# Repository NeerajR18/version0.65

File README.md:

# version0.65

version0.65 is an almost 65% keyboard. It is a bluetooth keyboard, using the SuperMini nRF52840 board, which is pin compatible with the nice!nano v2.
It has a built in battery along with a On/Off switch.

The keyboard is hotswap, with gateron hotswap sockets and Gateron Blue switches.

The PCB was designed in KiCad and the case was designed in Autodesk Fusion. The footprints for the switches have been taken from the marbastlib library - https://github.com/ebastler/marbastlib

This Keyboard was made for Hack Club KEEB.

Note: This is still a WIP. Please copy at your own risk.

## Repository Guide
```
version1/
|── PCB/
|   |── version0.65.kicad_pro
|   |── version0.65.kicad_pcb
|   |── version0.65.kicad_sch
|   └── fp-lib-table
|
|── CAD/
|   |── Base/
|   |   |── version0.65-base-left.step
|   |   |── version0.65-base-middle.step
|   |   └── version0.65-base-right.step
|   |   
|   |──── Top/
|   |     |── version0.65-plate-left.step
|   |     └── version0.65-plate-right.step
|   |
|   |── version0.65-assembly.step
|   └── version0.65.f3z
| 
|── Production/   
|    |── gerbers.zip/
|    |
|    |── STL Files/
|    |   |─── version0.65-base/
|    |   |    |── version0.65-base-left.stl
|    |   |    |── version0.65-base-middle.stl
|    |   |    └── version0.65-base-right.stl
|    |   |
|    |   └─── version0.65-plate/
|    |        |── version0.65-plate-left.stl
|    |        └── version0.65-plate-right.stl
|    |
|    └── STEP Files/
|           |─── version0.65-base/
|           |      |── version0.65-base-left.step
|           |      |── version0.65-base-middle.step
|           |      └── version0.65-base-right.step
|           |
|           └──── version0.65-plate/
|                   |── version0.65-plate-left.step
|                   └── version0.65-plate-right.step
|
|── Assets/
|    |── Keycaps/
|    |── MX Switch/
|    └── nice!nano/
|
|── Firmware/
|
|── BOM.csv
|── journal.md
└── README.md
```

## Schematic
##### Overall Schematic

## PCB
##### PCB Front without GND Plane

##### PCB Front with GND Plane

##### PCB Back without GND Plane

##### PCB Back with GND Plane

## CAD
The case has been split to accomodate 3D printing. The plates and base have small pegs and holes for assembly.

#### Full Assembly
##### Top View

#####  Side View

#### Top Plate
##### Top View

#####  Side View

#### Base
##### Top View

#####  Side View

## Firmware
version0.65 uses ZMK firmare. While the firmware has not been tested IRL, it can be found in a separate repository.

Firmware repository- https://github.com/NeerajR18/zmk-config-version0.65

## Bill of Materials
| Part Name | Quantity | Unit Price (USD) | Ext. Price (USD) | Link |
|-----------|---------:|-----------------:|-----------------:|------|
| nRF52840 Development Board (Compatible with nice!nano) | 1 | 8.00 | 8.00 | https://robu.in/product/promicro-nrf52840-development-board/ |
| Gradient Keycaps | 1 | 13.66 | 13.66 | https://stackskb.com/store/veekos-gradient-keycaps-cherry-profile-135-keys/ |
| Gateron Hotswap Sockets | 66 | 0.11 | 7.00 | https://stackskb.com/store/gateron-hotswap-sockets/ |
| Gateron G Pro 3.0 Switch (Pack of 10) | 7 | 2.10 | 14.71 | https://meckeys.com/shop/accessories/keyboard-accessories/key-switches/gateron-g-pro-3-0-switch/ |
| OS102011MA1QN1 | 1 | 0.38 | 0.38 | https://robu.in/product/os102011ma1qn1-ck-100ma-single-pole-double-throw-spdt-12v-10000-times-plugin-slide-switches-rohs/ |
| S2B-PH-SM4-TB | 1 | 0.42 | 0.42 | https://robu.in/product/s2b-ph-sm4-tblfsn-jst-1x2p-2p-ph-tin-2-25%E2%84%8385%E2%84%83-2a-1-2mm-copper-alloy-horizontal-attachment-smdp2mmsurface-mount%EF%BC%8Cright-angle-wire-to-board-connector-rohs/ |
| 1N4148W-T4 | 66 | 0.015 | 0.99 | https://sharvielectronics.com/product/1n4148w-t4-high-speed-fast-switching-diode-sod-123-package/ |
| YY503040-JST-PH | 1 | 2.31 | 2.31 | https://sharvielectronics.com/product/3-7v-1100mah-lipo-rechargeable-battery-with-jst-ph-2mm-connector/ |
| PCB from Robu | 5 | 8.83 | 44.28 | https://robu.in/ |
| Cherry Stabilizer Set (GEON AND C3) | 1 | 7.36 | 7.36 | https://neomacro.in/products/cherry-stabilizer-set-geon-and-c3?_pos=3&_sid=9a6134911&_ss=r |
| M3 Heatset Insert | 20 | 0.025 | 0.50 | https://onlyscrews.in/products/m3-x-3mm-brass-threaded-inserts |
| M3 × 16mm Screws | 20 | 0.023 | 0.46 | https://onlyscrews.in/products/hex-allen-csk-m3-x-16-screw-pack-of-20 |
| Shipping charges |-| - | 7 | - |
| **Total** |  |  | **107.07** |  |

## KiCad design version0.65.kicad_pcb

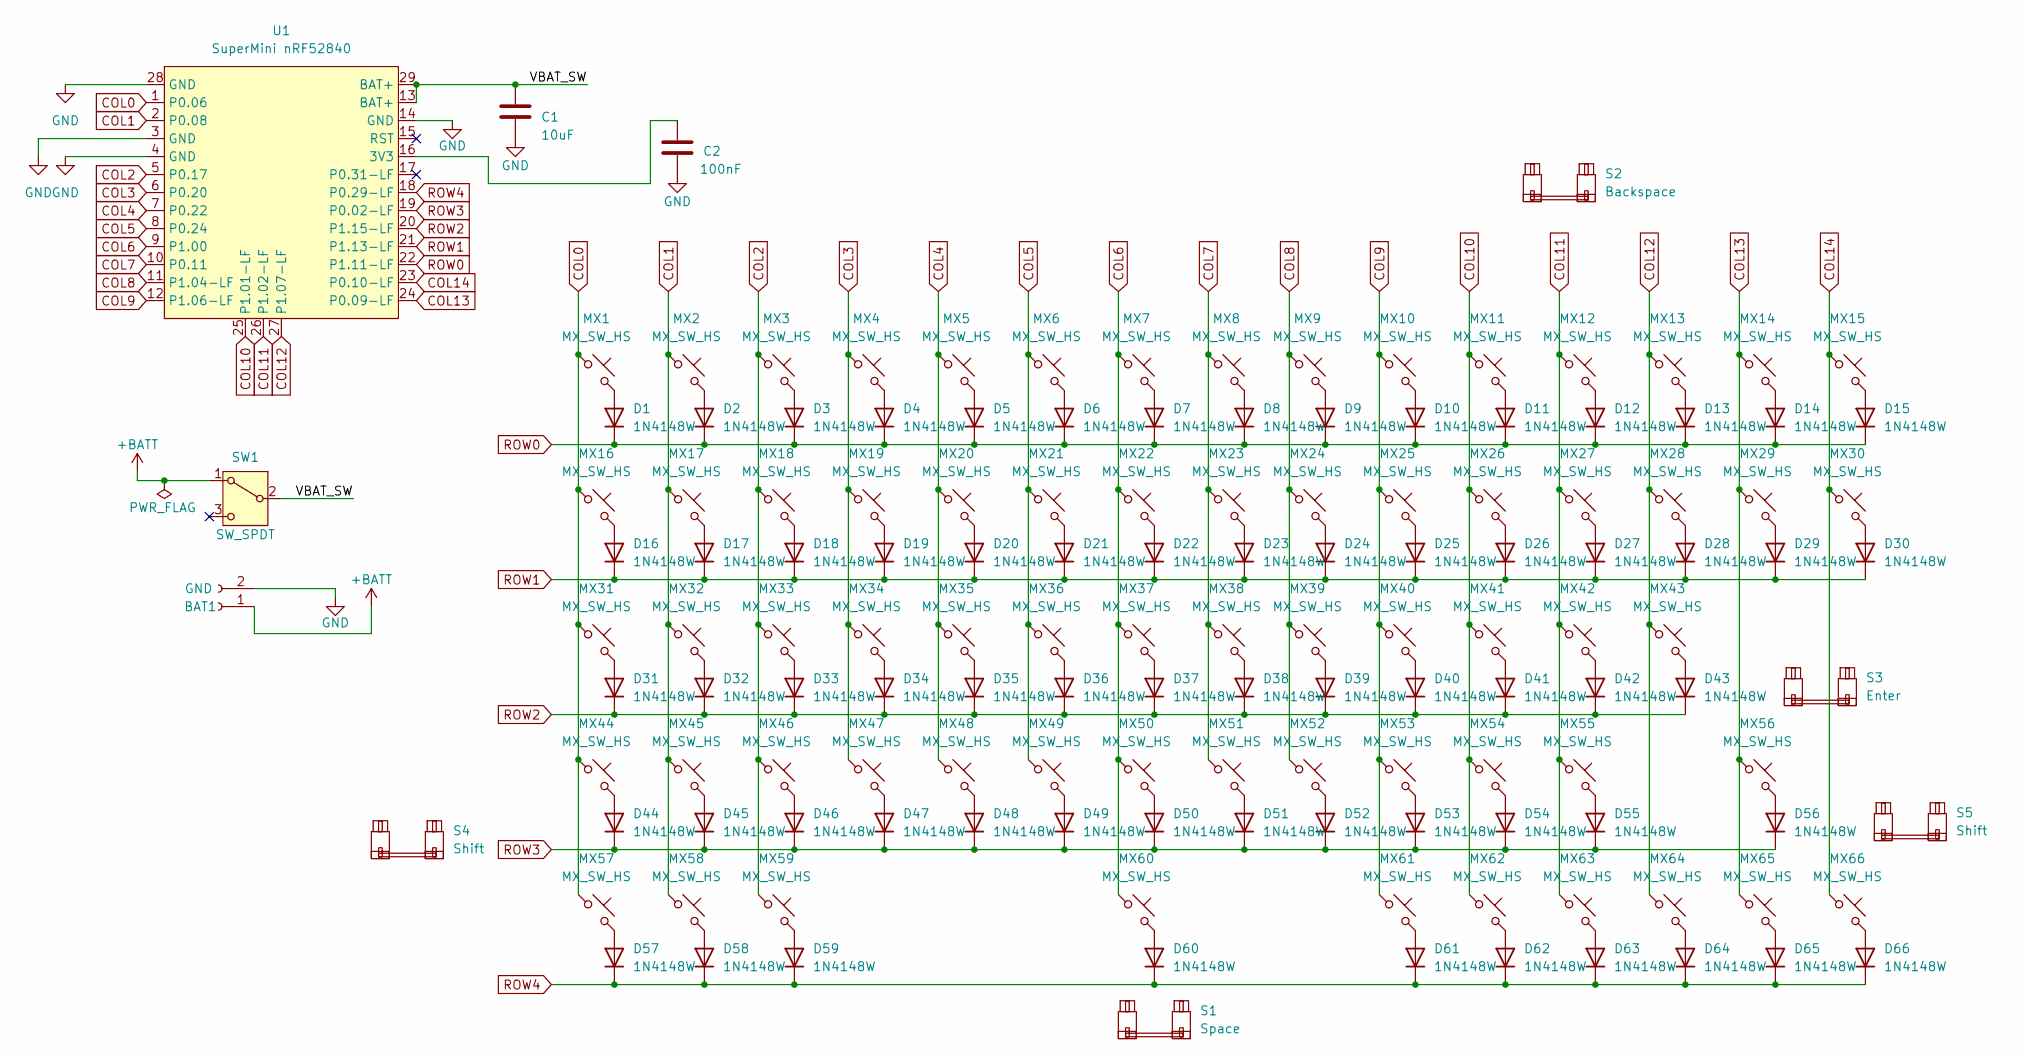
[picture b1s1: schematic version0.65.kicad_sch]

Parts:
BAT1: GND; JST_PH_S2B-PH-K_1x02_P2.00mm_Horizontal
C1: 10uF; C_0805_2012Metric
C2: 100nF; C_0805_2012Metric
D1, D2, D3, D4, D5, D6, D7, D8, D9, D10, D11, D12, D13, D14, D15, D16, D17, D18, D19, D20, D21, D22, D23, D24, D25, D26, D27, D28, D29, D30, D31, D32, D33, D34, D35, D36, D37, D38, D39, D40, D41, D42, D43, D44, D45, D46, D47, D48, D49, D50, D51, D52, D53, D54, D55, D56, D57, D58, D59, D60, D61, D62, D63, D64, D65, D66: 1N4148W; D_SOD-123
MX1, MX2, MX3, MX4, MX5, MX6, MX7, MX8, MX9, MX10, MX11, MX12, MX13, MX14, MX15, MX17, MX18, MX19, MX20, MX21, MX22, MX23, MX24, MX25, MX26, MX27, MX28, MX30, MX32, MX33, MX34, MX35, MX36, MX37, MX38, MX39, MX40, MX41, MX42, MX43, MX44, MX45, MX46, MX47, MX48, MX49, MX50, MX51, MX52, MX53, MX54, MX55, MX56, MX58, MX60, MX64, MX65, MX66: MX_SW_HS; SW_MX_HS_KS-2P02B01-01_1u
MX16, MX29: MX_SW_HS; SW_MX_HS_KS-2P02B01-01_1.5u
MX31: MX_SW_HS; SW_MX_HS_KS-2P02B01-01_1.75u
MX57, MX59, MX61, MX62, MX63: MX_SW_HS; SW_MX_HS_KS-2P02B01-01_1.25u
S1: Space; STAB_MX_P_6.25u
S2: Backspace; STAB_MX_2u
S3: Enter; STAB_MX_2.25u
S4, S5: Shift; STAB_MX_2.25u
SW1: SW_SPDT; SW_Slide_SPDT_Angled_CK_OS102011MA1Q
U1: SuperMini nRF52840; SuperMini_nRF52840_AH_USBup

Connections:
+BATT: BAT1.1, SW1.1 (A)
/VBAT_SW: C1.2, SW1.2 (B), U1.13 (BAT+), U1.29 (BAT+)
COL0: MX1.1, MX16.1, MX31.1, MX44.1, MX57.1, U1.1 (P0.06)
COL1: MX2.1, MX17.1, MX32.1, MX45.1, MX58.1, U1.2 (P0.08)
COL2: MX3.1, MX18.1, MX33.1, MX46.1, MX59.1, U1.5 (P0.17)
COL3: MX4.1, MX19.1, MX34.1, MX47.1, U1.6 (P0.20)
COL4: MX5.1, MX20.1, MX35.1, MX48.1, U1.7 (P0.22)
COL5: MX6.1, MX21.1, MX36.1, MX49.1, U1.8 (P0.24)
COL6: MX7.1, MX22.1, MX37.1, MX50.1, MX60.1, U1.9 (P1.00)
COL7: MX8.1, MX23.1, MX38.1, MX51.1, U1.10 (P0.11)
COL8: MX9.1, MX24.1, MX39.1, MX52.1, U1.11 (P1.04-LF)
COL9: MX10.1, MX25.1, MX40.1, MX53.1, MX61.1, U1.12 (P1.06-LF)
COL10: MX11.1, MX26.1, MX41.1, MX54.1, MX62.1, U1.25 (P1.01-LF)
COL11: MX12.1, MX27.1, MX42.1, MX55.1, MX63.1, U1.26 (P1.02-LF)
COL12: MX13.1, MX28.1, MX43.1, MX64.1, U1.27 (P1.07-LF)
COL13: MX14.1, MX29.1, MX56.1, MX65.1, U1.24 (P0.09-LF)
COL14: MX15.1, MX30.1, MX66.1, U1.23 (P0.10-LF)
GND: BAT1.2, C1.1, C2.1, U1.3 (GND), U1.4 (GND), U1.14 (GND), U1.28 (GND)
unnamed: D1.2 (A), MX1.2
unnamed: D2.2 (A), MX2.2
unnamed: D3.2 (A), MX3.2
unnamed: D4.2 (A), MX4.2
unnamed: D5.2 (A), MX5.2
unnamed: D6.2 (A), MX6.2
unnamed: D7.2 (A), MX7.2
unnamed: D8.2 (A), MX8.2
unnamed: D9.2 (A), MX9.2
unnamed: D10.2 (A), MX10.2
unnamed: D11.2 (A), MX11.2
unnamed: D12.2 (A), MX12.2
unnamed: D13.2 (A), MX13.2
unnamed: D14.2 (A), MX14.2
unnamed: D15.2 (A), MX15.2
unnamed: D16.2 (A), MX16.2
unnamed: D17.2 (A), MX17.2
unnamed: D18.2 (A), MX18.2
unnamed: D19.2 (A), MX19.2
unnamed: D20.2 (A), MX20.2
unnamed: D21.2 (A), MX21.2
unnamed: D22.2 (A), MX22.2
unnamed: D23.2 (A), MX23.2
unnamed: D24.2 (A), MX24.2
unnamed: D25.2 (A), MX25.2
unnamed: D26.2 (A), MX26.2
unnamed: D27.2 (A), MX27.2
unnamed: D28.2 (A), MX28.2
unnamed: D29.2 (A), MX29.2
unnamed: D30.2 (A), MX30.2
unnamed: D31.2 (A), MX31.2
unnamed: D32.2 (A), MX32.2
unnamed: D33.2 (A), MX33.2
unnamed: D34.2 (A), MX34.2
unnamed: D35.2 (A), MX35.2
unnamed: D36.2 (A), MX36.2
unnamed: D37.2 (A), MX37.2
unnamed: D38.2 (A), MX38.2
unnamed: D39.2 (A), MX39.2
unnamed: D40.2 (A), MX40.2
unnamed: D41.2 (A), MX41.2
unnamed: D42.2 (A), MX42.2
unnamed: D43.2 (A), MX43.2
unnamed: D44.2 (A), MX44.2
unnamed: D45.2 (A), MX45.2
unnamed: D46.2 (A), MX46.2
unnamed: D47.2 (A), MX47.2
unnamed: D48.2 (A), MX48.2
unnamed: D49.2 (A), MX49.2
unnamed: D50.2 (A), MX50.2
unnamed: D51.2 (A), MX51.2
unnamed: D52.2 (A), MX52.2
unnamed: D53.2 (A), MX53.2
unnamed: D54.2 (A), MX54.2
unnamed: D55.2 (A), MX55.2
unnamed: D56.2 (A), MX56.2
unnamed: D57.2 (A), MX57.2
unnamed: D58.2 (A), MX58.2
unnamed: D59.2 (A), MX59.2
unnamed: D60.2 (A), MX60.2
unnamed: D61.2 (A), MX61.2
unnamed: D62.2 (A), MX62.2
unnamed: D63.2 (A), MX63.2
unnamed: D64.2 (A), MX64.2
unnamed: D65.2 (A), MX65.2
unnamed: D66.2 (A), MX66.2
unnamed: C2.2, U1.16 (3V3)
ROW0: D1.1 (K), D2.1 (K), D3.1 (K), D4.1 (K), D5.1 (K), D6.1 (K), D7.1 (K), D8.1 (K), D9.1 (K), D10.1 (K), D11.1 (K), D12.1 (K), D13.1 (K), D14.1 (K), D15.1 (K), U1.22 (P1.11-LF)
ROW1: D16.1 (K), D17.1 (K), D18.1 (K), D19.1 (K), D20.1 (K), D21.1 (K), D22.1 (K), D23.1 (K), D24.1 (K), D25.1 (K), D26.1 (K), D27.1 (K), D28.1 (K), D29.1 (K), D30.1 (K), U1.21 (P1.13-LF)
ROW2: D31.1 (K), D32.1 (K), D33.1 (K), D34.1 (K), D35.1 (K), D36.1 (K), D37.1 (K), D38.1 (K), D39.1 (K), D40.1 (K), D41.1 (K), D42.1 (K), D43.1 (K), U1.20 (P1.15-LF)
ROW3: D44.1 (K), D45.1 (K), D46.1 (K), D47.1 (K), D48.1 (K), D49.1 (K), D50.1 (K), D51.1 (K), D52.1 (K), D53.1 (K), D54.1 (K), D55.1 (K), D56.1 (K), U1.19 (P0.02-LF)
ROW4: D57.1 (K), D58.1 (K), D59.1 (K), D60.1 (K), D61.1 (K), D62.1 (K), D63.1 (K), D64.1 (K), D65.1 (K), D66.1 (K), U1.18 (P0.29-LF)

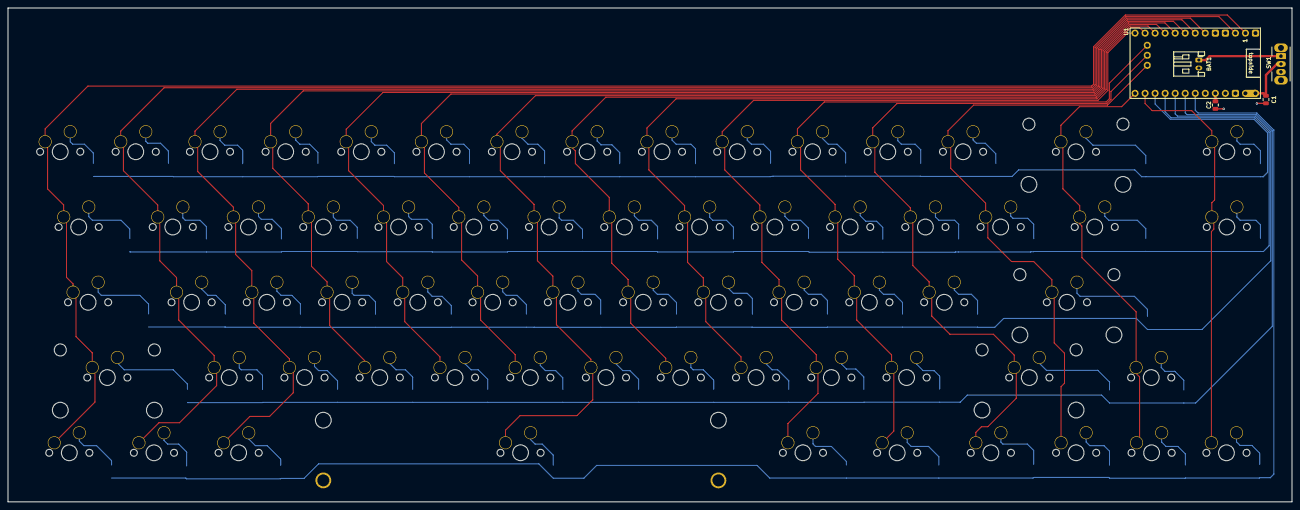
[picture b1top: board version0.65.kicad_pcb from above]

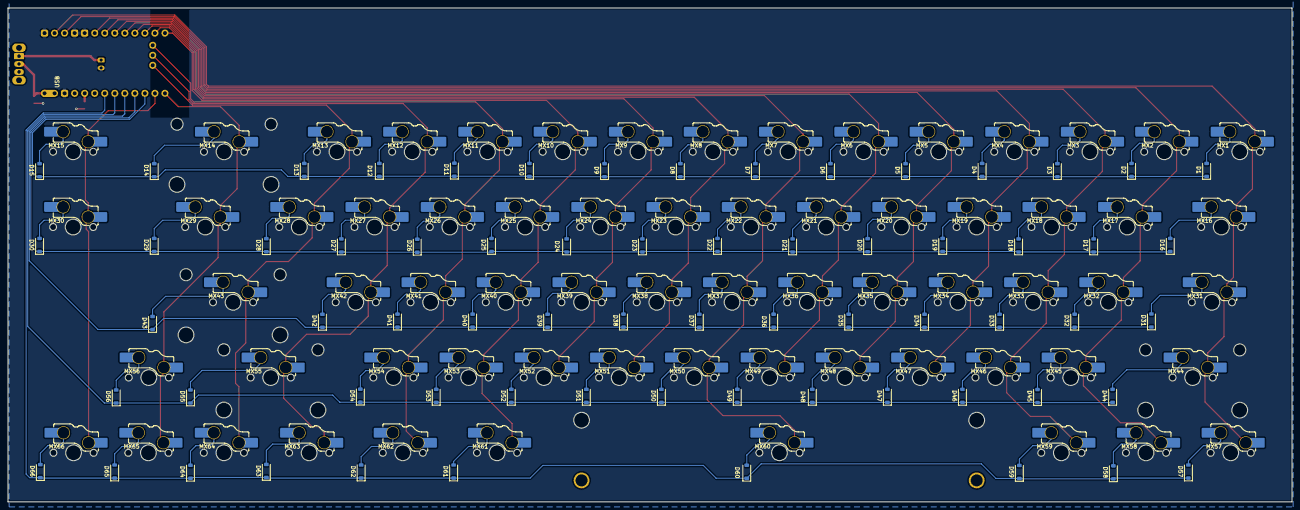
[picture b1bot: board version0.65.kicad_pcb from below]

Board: 2 copper layers, 325.0 x 125.0 mm, 142 parts (133 on the bottom side), 90 nets.

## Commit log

2026-06-05 Added 3D models to PCB and journal.md without images
2026-06-14 Added PCB and CAD files along with gerbers
2026-06-14 Added ZMK files
2026-06-14 Remove broken firmware submodule
2026-06-14 Remove misplaced submodule
2026-06-14 Add firmware submodule
2026-06-14 Updated journal with images
2026-06-14 Updated README
    Expanded the README.md to include detailed information about the version0.65 keyboard, its components, and repository structure.
2026-06-14 Added Production Files, BOM, Assets and CAD files
2026-06-28 Updated PCB files
2026-06-28 Document PCB and case redesign in journal
2026-06-28 Revise CAD folder structure and update images
2026-06-28 Updated CAD Files and stl files for production
2026-06-29 Update README.md with PCB images and BOM
